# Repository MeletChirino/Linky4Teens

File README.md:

# Linky4Teens
This is the official repository of the project Linky4Teens developped by:

- CHIRINO CAICEDO Melet
- LABIT Yann

## Planning

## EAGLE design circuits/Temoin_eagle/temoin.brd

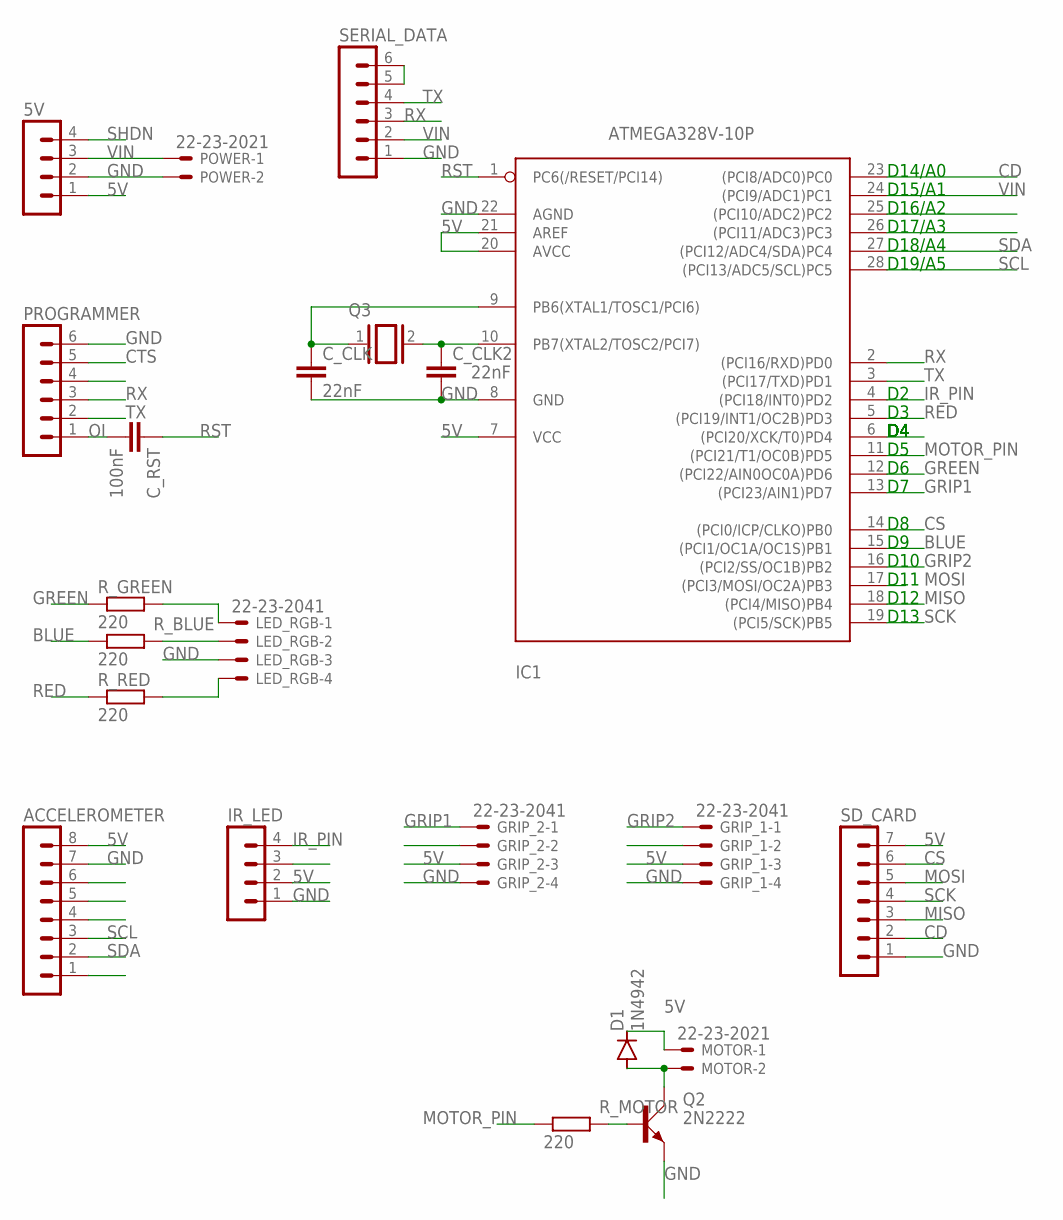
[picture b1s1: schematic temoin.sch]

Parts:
5V: MA04-1
ACCELEROMETER: MA08-1
C_CLK, C_CLK2: 22nF; C025-025X050
C_RST: 100nF; C025-040X050
D1: 1N4942; DO41-10
GRIP_1, GRIP_2: 22-23-2041
IC1: ATMEGA328V-10P; DIL28-3
IR_LED: MA04-1
LED_RGB: 22-23-2041
MOTOR: 22-23-2021
POWER: 22-23-2021
PROGRAMMER: MA06-1
Q2: 2N2222; TO18A
Q3: XTAL/S; QS
R_BLUE: 220; 0411/12
R_GREEN: 220; 0411/12
R_MOTOR: 220; 0411/12
R_RED: 220; 0411/12
SD_CARD: MA07-1
SERIAL_DATA: MA06-1

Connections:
5V: 5V.1, ACCELEROMETER.8, D1.C, GRIP_1.3, GRIP_2.3, IC1.7 (VCC), IC1.20 (AVCC), IC1.21 (AREF), IR_LED.2, MOTOR.1, SD_CARD.7
BLUE: IC1.15 ((PCI1/OC1A/OC1S)PB1), R_BLUE.1
CD: IC1.23 ((PCI8/ADC0)PC0), SD_CARD.2
CS: IC1.14 ((PCI0/ICP/CLKO)PB0), SD_CARD.6
CTS: PROGRAMMER.5
GND: 5V.2, ACCELEROMETER.7, C_CLK.2, C_CLK2.2, GRIP_1.4, GRIP_2.4, IC1.8 (GND), IC1.22 (AGND), IR_LED.1, LED_RGB.3, POWER.2, PROGRAMMER.6, Q2.E, SD_CARD.1, SERIAL_DATA.1
GREEN: IC1.12 ((PCI22/AIN0OC0A)PD6), R_GREEN.1
GRIP1: GRIP_2.1, IC1.13 ((PCI23/AIN1)PD7)
GRIP2: GRIP_1.1, IC1.16 ((PCI2/SS/OC1B)PB2)
IR_PIN: IC1.4 ((PCI18/INT0)PD2), IR_LED.4
MISO: IC1.18 ((PCI4/MISO)PB4), SD_CARD.3
MOSI: IC1.17 ((PCI3/MOSI/OC2A)PB3), SD_CARD.5
MOTOR_PIN: IC1.11 ((PCI21/T1/OC0B)PD5), R_MOTOR.1
unnamed: LED_RGB.2, R_BLUE.2
unnamed: SERIAL_DATA.5, SERIAL_DATA.6
unnamed: D1.A, MOTOR.2, Q2.C
unnamed: Q2.B, R_MOTOR.2
unnamed: C_CLK2.1, IC1.10 (PB7(XTAL2/TOSC2/PCI7)), Q3.2
unnamed: LED_RGB.1, R_GREEN.2
unnamed: LED_RGB.4, R_RED.2
unnamed: C_CLK.1, IC1.9 (PB6(XTAL1/TOSC1/PCI6)), Q3.1
OI: C_RST.2, PROGRAMMER.1
RED: IC1.5 ((PCI19/INT1/OC2B)PD3), R_RED.1
RST: C_RST.1, IC1.1 (PC6(/RESET/PCI14))
RX: IC1.2 ((PCI16/RXD)PD0), PROGRAMMER.3, SERIAL_DATA.3
SCK: IC1.19 ((PCI5/SCK)PB5), SD_CARD.4
SCL: ACCELEROMETER.3, IC1.28 ((PCI13/ADC5/SCL)PC5)
SDA: ACCELEROMETER.2, IC1.27 ((PCI12/ADC4/SDA)PC4)
SHDN: 5V.4
TX: IC1.3 ((PCI17/TXD)PD1), PROGRAMMER.2, SERIAL_DATA.4
VIN: 5V.3, IC1.24 ((PCI9/ADC1)PC1), POWER.1, SERIAL_DATA.2

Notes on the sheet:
D10
D11
D12
D13
D14/A0
D15/A1
D16/A2
D17/A3
D18/A4
D19/A5

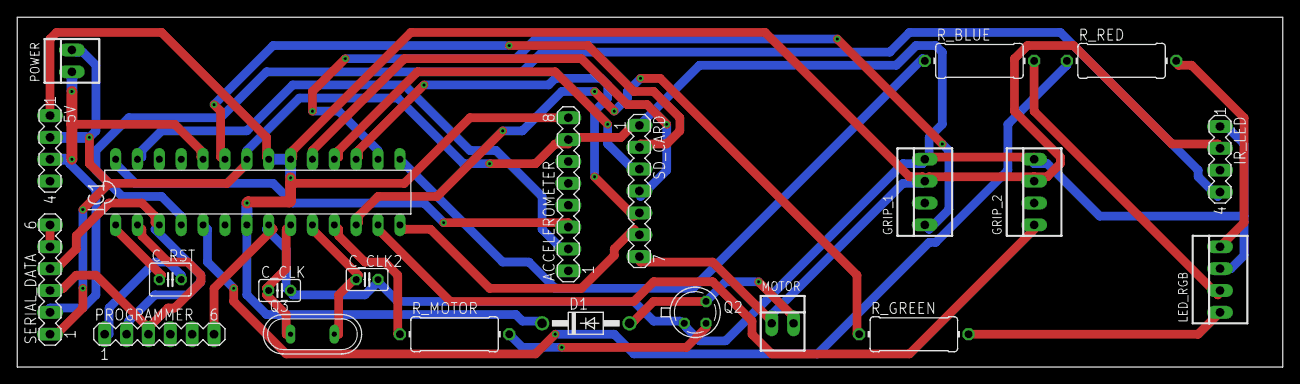
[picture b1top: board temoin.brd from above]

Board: 2 copper layers, 147.0 x 40.6 mm, 22 parts (0 on the bottom side), 29 nets.

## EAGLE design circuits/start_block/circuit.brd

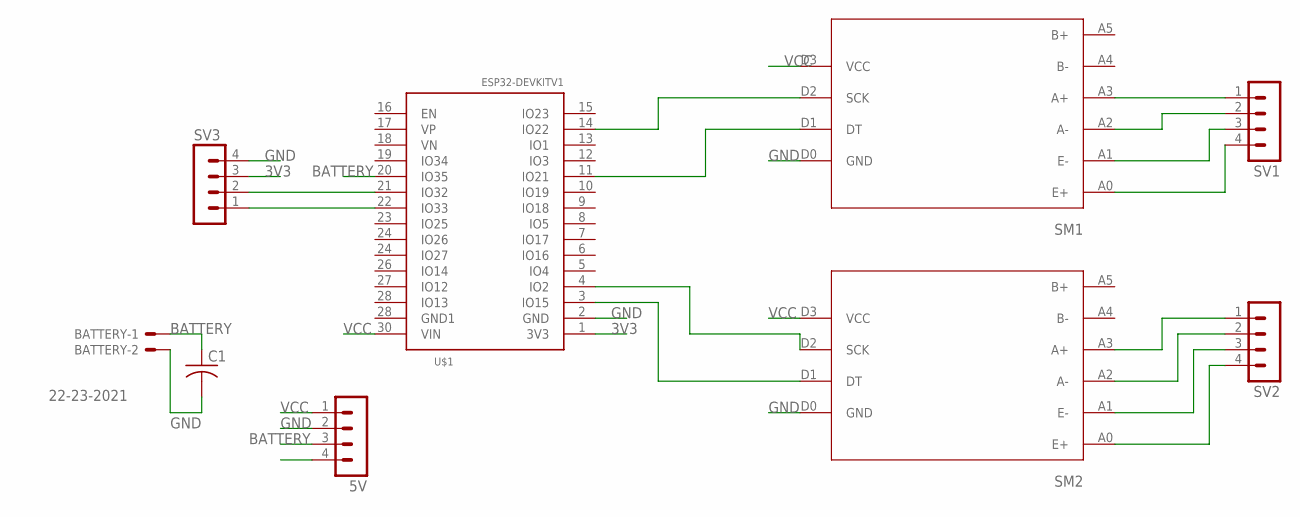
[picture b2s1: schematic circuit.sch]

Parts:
5V: MA04-1
BATTERY: 22-23-2021
C1: C-US050-055X075; C050-055X075
SM1, SM2: HX711
SV1, SV2, SV3: MA04-1
U$1: ESP32DEVKITV1; ESP32-DEVKITV1

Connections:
3V3: SV3.3, U$1.1 (3V3)
BATTERY: 5V.3, BATTERY.1, C1.1, U$1.20 (IO35)
GND: 5V.2, BATTERY.2, C1.2, SM1.D0 (GND), SM2.D0 (GND), SV3.4, U$1.2 (GND)
unnamed: SM2.A0 (E+), SV2.4
unnamed: SM2.A1 (E-), SV2.3
unnamed: SM2.A2 (A-), SV2.2
unnamed: SM2.A3 (A+), SV2.1
unnamed: SM1.A0 (E+), SV1.4
unnamed: SM1.A1 (E-), SV1.3
unnamed: SM1.A2 (A-), SV1.2
unnamed: SM1.A3 (A+), SV1.1
unnamed: SM1.D2 (SCK), U$1.14 (IO22)
unnamed: SM1.D1 (DT), U$1.11 (IO21)
unnamed: SM2.D1 (DT), U$1.3 (IO15)
unnamed: SM2.D2 (SCK), U$1.4 (IO2)
unnamed: SV3.2, U$1.21 (IO32)
unnamed: SV3.1, U$1.22 (IO33)
VCC: 5V.1, SM1.D3 (VCC), SM2.D3 (VCC), U$1.30 (VIN)

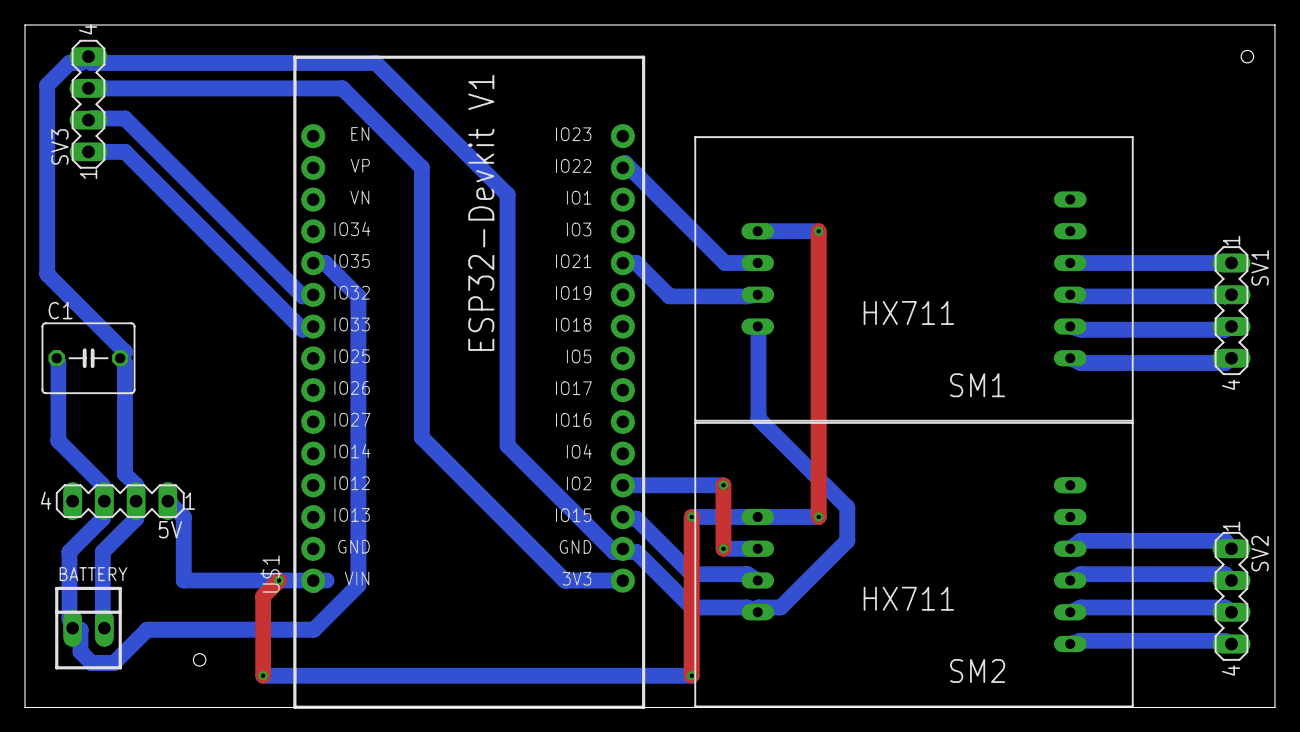
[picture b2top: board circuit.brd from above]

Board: 2 copper layers, 100.0 x 54.6 mm, 9 parts (0 on the bottom side), 18 nets.

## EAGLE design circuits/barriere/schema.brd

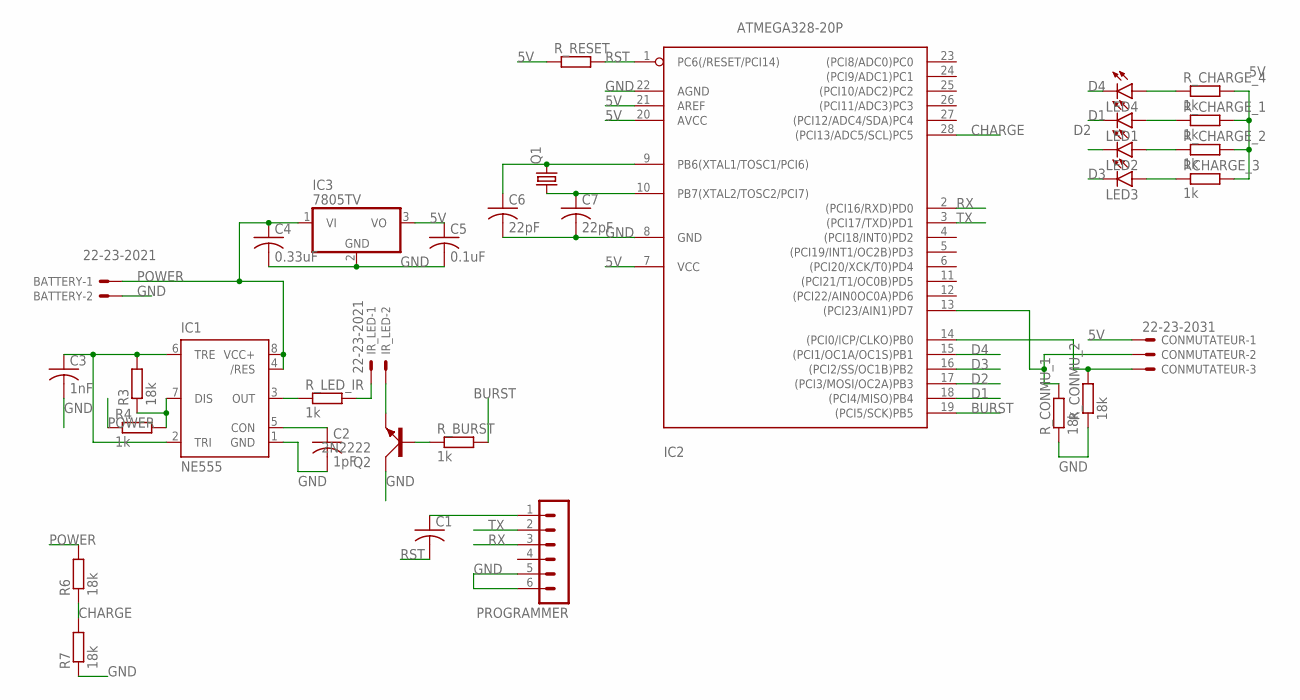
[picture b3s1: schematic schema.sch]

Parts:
BATTERY: 22-23-2021
C1: C-US050-024X044; C050-024X044
C2: 1pF; C050-024X044
C3: 1nF; C050-024X044
C4: 0.33uF; C050-024X044
C5: 0.1uF; C050-024X044
C6, C7: 22pF; C050-024X044
CONMUTATEUR: 22-23-2031
IC1: NE555; DIL-08
IC2: ATMEGA328-20P; DIL28-3
IC3: 7805TV; TO220V
IR_LED: 22-23-2021
LED1, LED2, LED3, LED4: LED5MM
PROGRAMMER: MA06-1
Q1: CRYSTALHC49S; HC49/S
Q2: 2N2222; TO18A
R3, R6, R7: 18k; 0207/7
R4: 1k; 0207/7
RCHARGE_3: 1k; 0207/7
R_BURST: 1k; 0207/7
R_CHARGE_1, R_CHARGE_2, R_CHARGE_4: 1k; 0207/7
R_CONMU_1, R_CONMU_2: 18k; 0207/7
R_LED_IR: 1k; 0207/7
R_RESET: R-EU_0207/7; 0207/7

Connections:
5V: C5.1, CONMUTATEUR.1, IC2.7 (VCC), IC2.20 (AVCC), IC2.21 (AREF), IC3.3 (VO), RCHARGE_3.2, R_CHARGE_1.2, R_CHARGE_2.2, R_CHARGE_4.2, R_RESET.1
BURST: IC2.19 ((PCI5/SCK)PB5), R_BURST.2
CHARGE: IC2.28 ((PCI13/ADC5/SCL)PC5), R6.1, R7.2
D1: IC2.18 ((PCI4/MISO)PB4), LED1.K (C)
D2: IC2.17 ((PCI3/MOSI/OC2A)PB3), LED2.K (C)
D3: IC2.16 ((PCI2/SS/OC1B)PB2), LED3.K (C)
D4: IC2.15 ((PCI1/OC1A/OC1S)PB1), LED4.K (C)
GND: BATTERY.2, C2.2, C3.2, C4.2, C5.2, C6.2, C7.2, IC1.1 (GND), IC2.8 (GND), IC2.22 (AGND), IC3.2 (GND), PROGRAMMER.5, PROGRAMMER.6, Q2.C, R7.1, R_CONMU_1.1, R_CONMU_2.1
unnamed: IR_LED.1, R_LED_IR.2
unnamed: IC1.3 (OUT), R_LED_IR.1
unnamed: C2.1, IC1.5 (CON)
unnamed: IC1.7 (DIS), R3.1, R4.2
unnamed: C3.1, IC1.2 (TRI), IC1.6 (TRE), R3.2
unnamed: IR_LED.2, Q2.E
unnamed: CONMUTATEUR.2, IC2.13 ((PCI23/AIN1)PD7), R_CONMU_1.2
unnamed: C7.1, IC2.10 (PB7(XTAL2/TOSC2/PCI7)), Q1.1
unnamed: C6.1, IC2.9 (PB6(XTAL1/TOSC1/PCI6)), Q1.2
unnamed: Q2.B, R_BURST.1
unnamed: CONMUTATEUR.3, IC2.14 ((PCI0/ICP/CLKO)PB0), R_CONMU_2.2
unnamed: LED3.A, RCHARGE_3.1
unnamed: LED2.A, R_CHARGE_2.1
unnamed: LED1.A, R_CHARGE_1.1
unnamed: LED4.A, R_CHARGE_4.1
unnamed: C1.1, PROGRAMMER.1
POWER: BATTERY.1, C4.1, IC1.4 (/RES), IC1.8 (VCC+), IC3.1 (VI), R4.1, R6.2
RST: C1.2, IC2.1 (PC6(/RESET/PCI14)), R_RESET.2
RX: IC2.2 ((PCI16/RXD)PD0), PROGRAMMER.3
TX: IC2.3 ((PCI17/TXD)PD1), PROGRAMMER.2

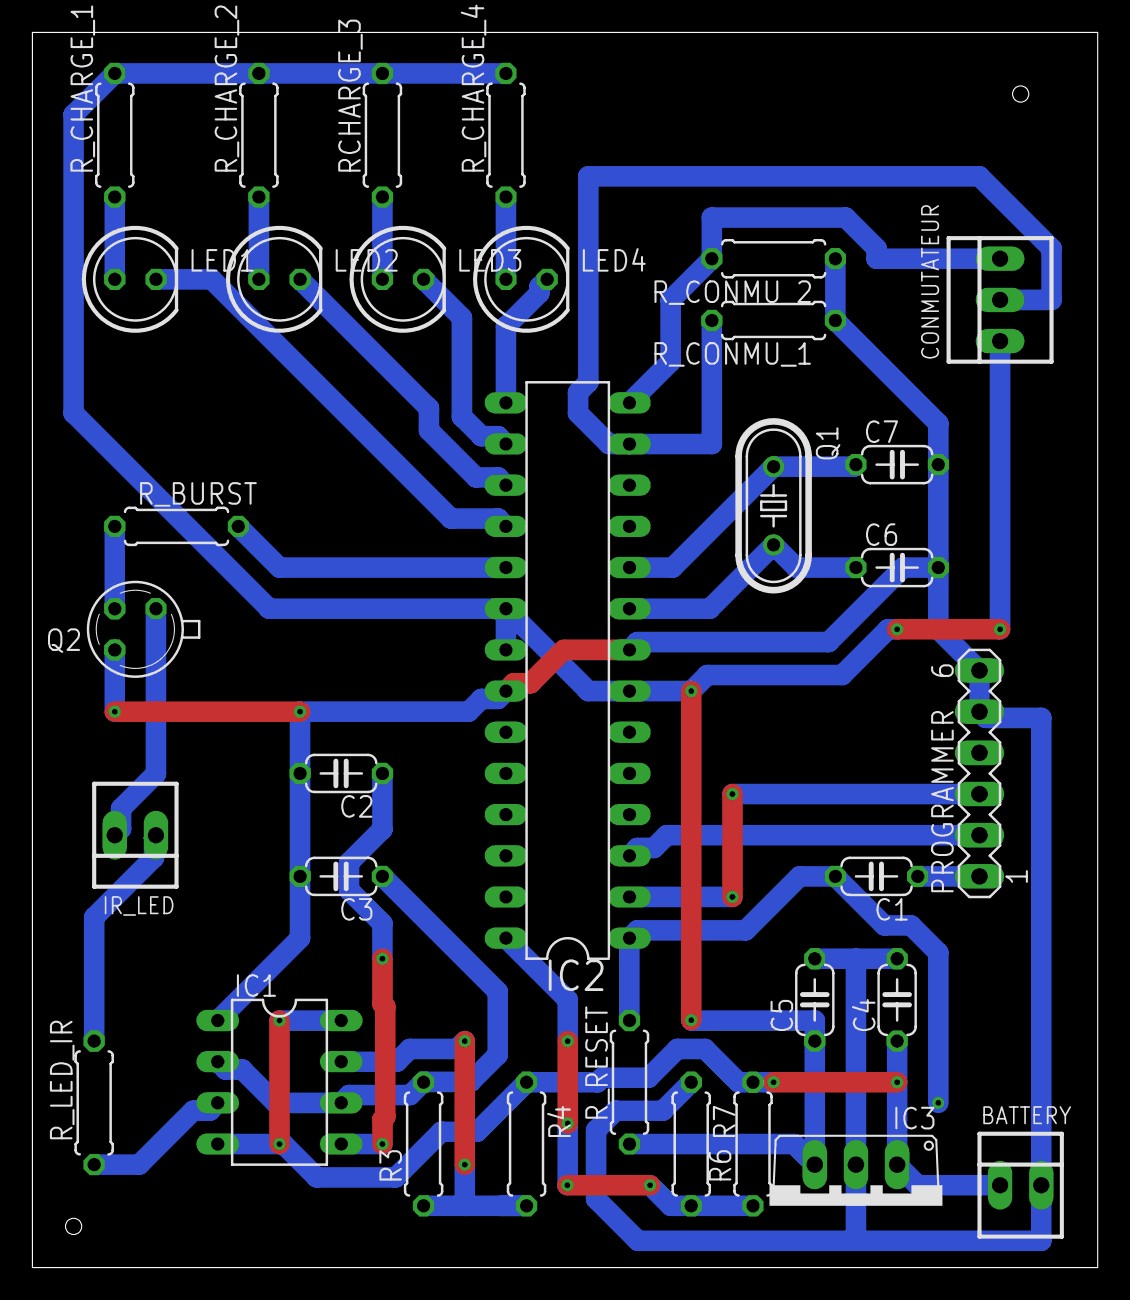
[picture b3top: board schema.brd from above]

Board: 2 copper layers, 65.7 x 76.2 mm, 33 parts (0 on the bottom side), 28 nets.

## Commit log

2021-04-26 Git init
2021-04-26 Gantt file added
2021-04-27 Liste de composants ajouté
2021-04-27 Liste corrigé
2021-04-30 Ajouté raspberry pi
2021-05-06 New circuit that transmit data in a modulated way to send messages to relay stick
2021-05-11 New Raspberry programs added, requierements file updated
2021-05-24 Libraries imported from last project. Also algorithm working for grip sensor when race started
2021-05-24 gitignore updated
2021-05-25 Arduino program updated to receive information thru serial port. Plus, requirements file updated and DATA.TXT file added
2021-05-26 Documentation added to arduino's program
2021-05-26 Documentation added to program for IR Barrier
2021-05-27 Documentation and gitignore updated
2021-06-01 installing script is ready
2021-06-01 script updated to install virtual environment as well
2021-06-01 Installing Script updated to install and configure apache2
2021-06-03 Its ok to send information thru serial port from the sd card (reading exemple data file)
2021-06-04 Esp32 connects to Raspberry and send data with different options
2021-06-05 Added necessary files to have GUI working
2021-06-08 settings file updated to support domain
2021-06-08 apps added
2021-06-08 html files modified
2021-06-08 plotting functions added
2021-06-08 start point send data as server
2021-06-08 plots are ok now
2021-06-08 last changes
2021-06-09 Now the program request data to other start block and draw 2 plots (each feet)
2021-06-09 Added View for creating athletes
2021-06-09 update athlete view added
2021-06-09 Home view added
2021-06-09 Connection timeout added to start point page
2021-06-09 Minor details added
2021-06-09 ESP32 send info to GUI
2021-06-18 New program for ir_sender, I have to rewrite everything un C++
2021-06-28 Update to programs
2021-06-28 Added commands to send data from actual hardware
2021-06-29 esp32 now sends actual info from sensors, it still need some calibration
2021-06-29 Changes to plot, save and show sensor information
2021-07-01 added circuits of temoins
2021-07-01 models updated
2021-07-04 Start point server is calibrated
2021-07-13 Now shows battery charge for starting block
2021-07-13 Now sends battery charge information to the server
2021-07-23 Some changes to make work last commit
2021-07-23 GUI changes and error solutions
2021-07-23 ESP32 sends data and reads the battery to the gui
2021-07-27 Relay app updated and functional
2021-07-27 Errors solved
2021-07-27 urls file for relays app added
2021-07-27 Untracked templates files added
2021-07-27 Starting block is more stable now, it will always send data, also has a led taht indicates whether connected or not
2021-07-27 git ignore updated and a little change
2021-07-27 Little bug in starting block solved
2021-07-27 "Cosmetic changes" for gui
2021-07-27 Files names' updates, nos shows athlete's name as well
2021-07-27 Little change to avoid a print in test server
2021-07-27 Circuit boards added
2021-07-27 Update view added
2021-07-27 Requierements.txt updated
2021-07-27 New middlware added for reading starting block battery everytime the browser refreshes
2021-07-27 Bug fixing
2021-07-27 Useless functions erased
2021-07-27 Cosmetic changes to make GUI look pretier
2021-07-28 Error pages added
2021-07-28 QR code for wifi direct connection
2021-08-06 UML diagrams added
2021-08-17 [ADD] Latex files added
2021-08-17 [UPDATED] gitignore updated to ignore latex trash files
2021-08-17 Description du systeme, Objetifs, ameliorations proposees
2021-08-17 Devoirs Administratifs
2021-08-17 Logiciels de CAO
2021-08-17 Service electronique y la mitad de campus fab
2021-08-17 Raspberry como dock, falta el trabajo futuro
2021-08-18 Modificaciones antes de la revision de adriano y colleen
2021-08-18 [UPDATED] Gitignore
2021-08-23 [UPDATED] revision de ortografia
2021-08-28 [ADD] latex file to show the stage
2021-08-29 Cambios en el archivo de la soutenance
2021-08-29 [UPDATE] Diagrama de componentes
